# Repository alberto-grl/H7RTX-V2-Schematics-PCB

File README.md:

Schematics and PCB for a three-band direct sampling SDR. Using the internal ADC of an MCU, TX power is about 5 W.    
USB powered.    
Firmware code: https://github.com/alberto-grl/750RTX

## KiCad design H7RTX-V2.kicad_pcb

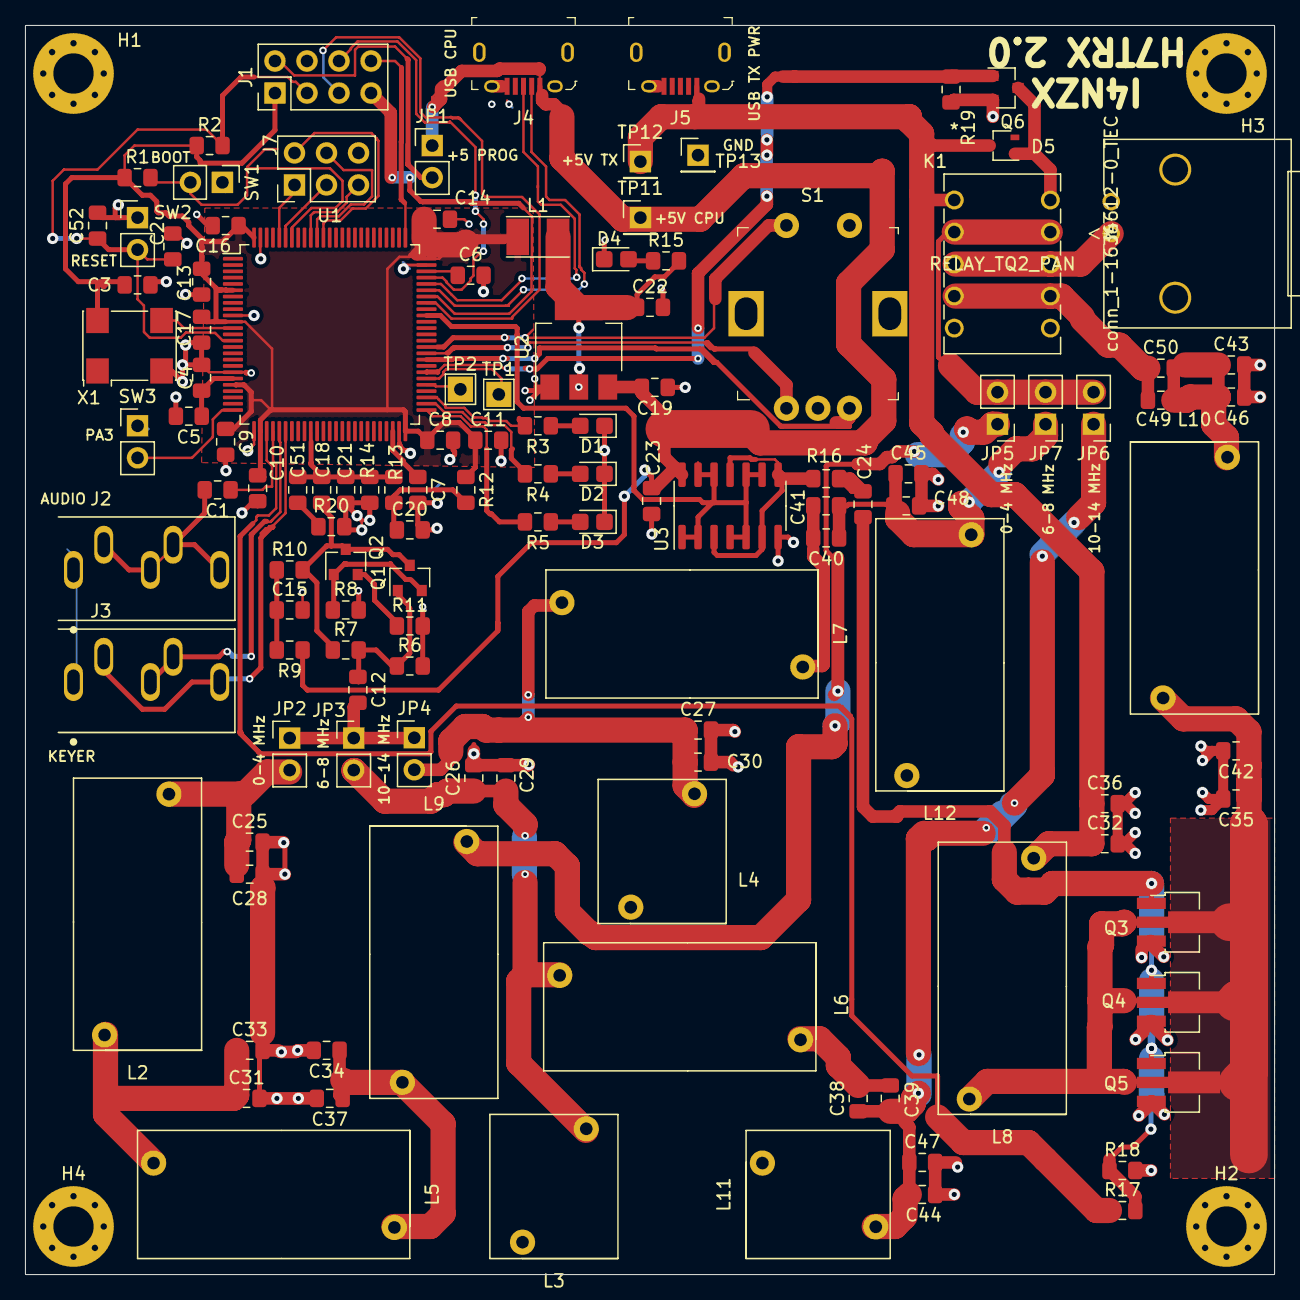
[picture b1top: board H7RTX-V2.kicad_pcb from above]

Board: 2 copper layers, 99.1 x 99.1 mm, 127 parts (0 on the bottom side), 71 nets.

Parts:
C1, C19, C22: 10u; C_0805_2012Metric_Pad1.15x1.40mm_HandSolder
C2, C3, C5, C6, C7, C8, C9, C10, C11, C13, C14, C17, C18, C23, C24, C32, C36, C49, C50: 100n; C_0805_2012Metric_Pad1.15x1.40mm_HandSolder
C4: 1u; C_0805_2012Metric_Pad1.15x1.40mm_HandSolder
C12, C51, C52: 10n; C_0805_2012Metric_Pad1.15x1.40mm_HandSolder
C15, C20: 470n; C_0805_2012Metric_Pad1.15x1.40mm_HandSolder
C16: 4.7u; C_0805_2012Metric_Pad1.15x1.40mm_HandSolder
C21, C39: 10p; C_0805_2012Metric_Pad1.15x1.40mm_HandSolder
C25: 2n; C_0805_2012Metric_Pad1.15x1.40mm_HandSolder
C26, C47: 2700p; C_0805_2012Metric_Pad1.15x1.40mm_HandSolder
C27, C30, C40, C41, C45, C48: C; C_0805_2012Metric_Pad1.15x1.40mm_HandSolder
C28, C31, C34: 0; C_0805_2012Metric_Pad1.15x1.40mm_HandSolder
C29, C44: 470p; C_0805_2012Metric_Pad1.15x1.40mm_HandSolder
C33: 1800p; C_0805_2012Metric_Pad1.15x1.40mm_HandSolder
C35, C42: 6800p; C_0805_2012Metric_Pad1.15x1.40mm_HandSolder
C37: 1000p; C_0805_2012Metric_Pad1.15x1.40mm_HandSolder
C38: 22p; C_0805_2012Metric_Pad1.15x1.40mm_HandSolder
C43: 470; C_0805_2012Metric_Pad1.15x1.40mm_HandSolder
C46: 2200p; C_0805_2012Metric_Pad1.15x1.40mm_HandSolder
D1, D4: RED; LED_0805_2012Metric_Castellated
D2: GREEN; LED_0805_2012Metric_Castellated
D3: YLW; LED_0805_2012Metric_Castellated
D5: BAS16W; SOT-323_SC-70
H1, H2, H3, H4: MountingHole_Pad; MountingHole_3.2mm_M3_Pad_Via
J1: Conn_02x04_Odd_Even; PinHeader_2x04_P2.54mm_Vertical
J2, J3: SJ1-3535NG; CUI_SJ1-3535NG
J4, J5: 10118194-0001LF; USB_Micro_B_Female_10118194-0001LF
J6: conn_1-1634612-0_TEC; 1-1634612-0
J7: Conn_02x03_Odd_Even; PinHeader_2x03_P2.54mm_Vertical
JP1, JP2, JP3, JP4, JP5, JP6, JP7: Jumper; PinHeader_1x02_P2.54mm_Vertical
K1: RELAY_TQ2_PAN; TQ2-5V
L1: NRH3012T100MN; L_Taiyo-Yuden_NR-30xx_HandSoldering
L2: 2.6u; Air_Wound_Coil_8x20
L3, L4: L; Air_Wound_Coil_8x10
L5: 4.3u; Air_Wound_Coil_8x20
L6: 16u; Air_Wound_Coil_8x20
L7, L12: L; Air_Wound_Coil_8x20
L8: 15u; Air_Wound_Coil_8x20
L9: 5.19u; Air_Wound_Coil_8x20
L10: 0.15u 8t 8mm x 15mm; Air_Wound_Coil_8x20
L11: 150n 5T 8 x 5; Air_Wound_Coil_8x10
Q1, Q2: PMBT2222A_215; SOT-23
Q3, Q4, Q5: ZXMN3A01ZTA; SOT-89-3_Handsoldering
Q6: BSS138; SOT-23
R1, R2: 10K; R_0805_2012Metric_Pad1.15x1.40mm_HandSolder
R3, R4, R5, R15: 220R; R_0805_2012Metric_Pad1.15x1.40mm_HandSolder
R6: 1200; R_0805_2012Metric_Pad1.15x1.40mm_HandSolder
R7: 1000; R_0805_2012Metric_Pad1.15x1.40mm_HandSolder
R8: 220; R_0805_2012Metric_Pad1.15x1.40mm_HandSolder
R9: 10; R_0805_2012Metric_Pad1.15x1.40mm_HandSolder
R10: 150; R_0805_2012Metric_Pad1.15x1.40mm_HandSolder
R11: 1.2; R_0805_2012Metric_Pad1.15x1.40mm_HandSolder
R12, R20: 100; R_0805_2012Metric_Pad1.15x1.40mm_HandSolder
R13, R14: 10k; R_0805_2012Metric_Pad1.15x1.40mm_HandSolder
R16: 2.2; R_0805_2012Metric_Pad1.15x1.40mm_HandSolder
R17: 1K; R_0805_2012Metric_Pad1.15x1.40mm_HandSolder
R18: 100K; R_0805_2012Metric_Pad1.15x1.40mm_HandSolder
R19: R; R_0805_2012Metric_Pad1.15x1.40mm_HandSolder
S1: PEC11R-4215F-S0024; Rotary_Encoder_Switched_PEC11R
SW1, SW2, SW3: SW_DIP_x01; PinHeader_1x02_P2.54mm_Vertical
TP1, TP2: TestPoint; TestPoint_THTPad_2.0x2.0mm_Drill1.0mm
TP11, TP12, TP13: TestPoint; PinHeader_1x01_P2.54mm_Vertical
U1: STM32H750VBT6; LQFP-100_14x14mm_P0.5mm
U2: AP1117-33; SOT-223-3_TabPin2
U3: 74ACT00DR; SOIC-14_3.9x8.7mm_P1.27mm
X1: ASV-25MHz; Oscillator_SMD_Abracon_ASV-4Pin_7.0x5.1mm

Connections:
+5V: C19.2, C23.1, J4.1, JP1.1, R9.1, TP11.1, U2.3, U3.14
+5VP: C32.1, C36.1, D5.3, J5.1, K1.1, L8.1, TP12.1
/BOOT: R1.2, SW1.2, U1.94
/I2C_SCL: J7.3, U1.95
/I2C_SDA: J7.1, U1.96
/KeyerDash: J3.3, J3.5, U1.30
/KeyerDot: J3.2, J3.4, U1.31
/PA3: SW3.2, U1.25
/PA4: C1.1, U1.28
/PB1: C18.1, C21.1, C51.1, R13.2, R14.1, U1.35
/PB3: J7.2, U1.89
/PB4: J7.4, U1.90
/PB5: J7.5, U1.91
/PB12: R5.2, U1.51
/PB13: R4.2, U1.52
/PB14: R3.2, U1.53
/PD8: TP2.1, U1.55
/PD9: TP1.1, U1.56
/PD12: S1.B, U1.59
/PD13: S1.A, U1.60
/PD14: S1.1, U1.61
/SWCLK: J1.8, U1.76
/SWDIO: J1.6, U1.72
/USB1_D+: J4.3, U1.71
/USB1_D-: J4.2, U1.70
/VCC_CPU: C3.1, C8.1, C9.1, C10.1, C11.1, C13.1, C14.1, C16.1, C17.1, J1.1, L1.1, R1.1, R2.1, R12.1, U1.6, U1.11, U1.21, U1.27, U1.50, U1.75, U1.100, X1.4
/VCP_RX: J1.7, U1.69
/VCP_TX: J1.5, U1.68
/nRESET: C2.1, C52.1, J1.3, R2.2, SW2.2, U1.14
GND: C2.2, C3.2, C4.2, C5.2, C6.2, C7.2, C8.2, C9.2, C10.2, C11.2, C13.2, C14.2, C15.2, C16.2, C17.2, C19.1, C20.2, C21.2, C22.2, C23.2, C25.2, C26.2, C27.2, C28.2, C29.2, C30.2, C31.2, C32.2, C33.2, C34.2, C35.2, C36.2, C37.2, C42.2, C43.2, C44.2, C45.2, C46.2, C47.2, C48.2, C52.2, D1.1, D2.1, D3.1, D4.1, H1.1, H2.1, H3.1, H4.1, J1.4, J2.1, J3.1, J4.5, J4.SH, J5.5, J5.SH, J6.2, J6.3, J6.4, J7.6, L3.2, L4.2, L11.2, L12.2, Q3.3, Q4.3, Q5.3, Q6.2, R6.2, R8.2, R11.2, R14.2, R18.2, R19.2, R20.2, S1.2, S1.3, S1.C, SW1.1, SW2.1, SW3.1, TP13.1, U1.10, U1.19, U1.26, U1.49, U1.74, U1.99, U2.1, U3.7, X1.2
MCO: U1.66, U3.1, U3.2, U3.4, U3.5, U3.9, U3.10, U3.12, U3.13
unnamed: C1.2, J2.2, J2.3, J2.4, J2.5
unnamed: C4.1, C5.1, U1.20
unnamed: C6.1, U1.73
unnamed: C7.1, U1.48
unnamed: C12.1, Q1.1, R6.1, R7.2
unnamed: C15.1, R9.2, R10.1
unnamed: C18.2, Q1.3, Q2.3, R7.1, R10.2
unnamed: C20.1, R12.2, R13.1
unnamed: C24.1, Q3.1, Q4.1, Q5.1, R17.2, R18.1
unnamed: C24.2, R16.1
unnamed: C25.1, C28.1, JP2.2, L2.1
unnamed: C26.1, C29.1, JP3.2, L3.1, L6.1
unnamed: C27.1, C30.1, JP4.2, L4.1, L7.1
unnamed: C31.1, C33.1, L2.2, L5.1
unnamed: C34.1, C37.1, L5.2, L9.1
unnamed: C35.1, C42.1, L8.2, L10.1, Q3.2, Q4.2, Q5.2
unnamed: C38.1, C39.1, C44.1, C47.1, JP6.1, L11.1
unnamed: C38.2, C39.2, L6.2
unnamed: C40.1, C41.1, C45.1, C48.1, JP7.1, L12.1
unnamed: C40.2, C41.2, L7.2
unnamed: C43.1, C46.1, C49.2, C50.2, L10.2
unnamed: C49.1, C50.1, K1.4, K1.7
unnamed: C51.2, R20.1
unnamed: D1.2, R3.1
unnamed: D2.2, R4.1
unnamed: D3.2, R5.1
unnamed: D4.2, R15.1
unnamed: D5.1, K1.10, Q6.3
unnamed: J1.2, JP1.2
unnamed: J6.1, K1.3, K1.8
unnamed: JP5.1, L9.2
unnamed: JP5.2, JP6.2, JP7.2, K1.2, K1.9
unnamed: Q1.2, Q2.1, R8.1
unnamed: Q2.2, R11.1
unnamed: R16.2, U3.3, U3.6, U3.8, U3.11
unnamed: U1.12, X1.3
RXTX: Q6.1, R19.1, U1.57
RX_IN: C12.2, JP2.1, JP3.1, JP4.1
TX_BIAS: R17.1, U1.29
VCC: C22.1, L1.2, R15.2, U2.2

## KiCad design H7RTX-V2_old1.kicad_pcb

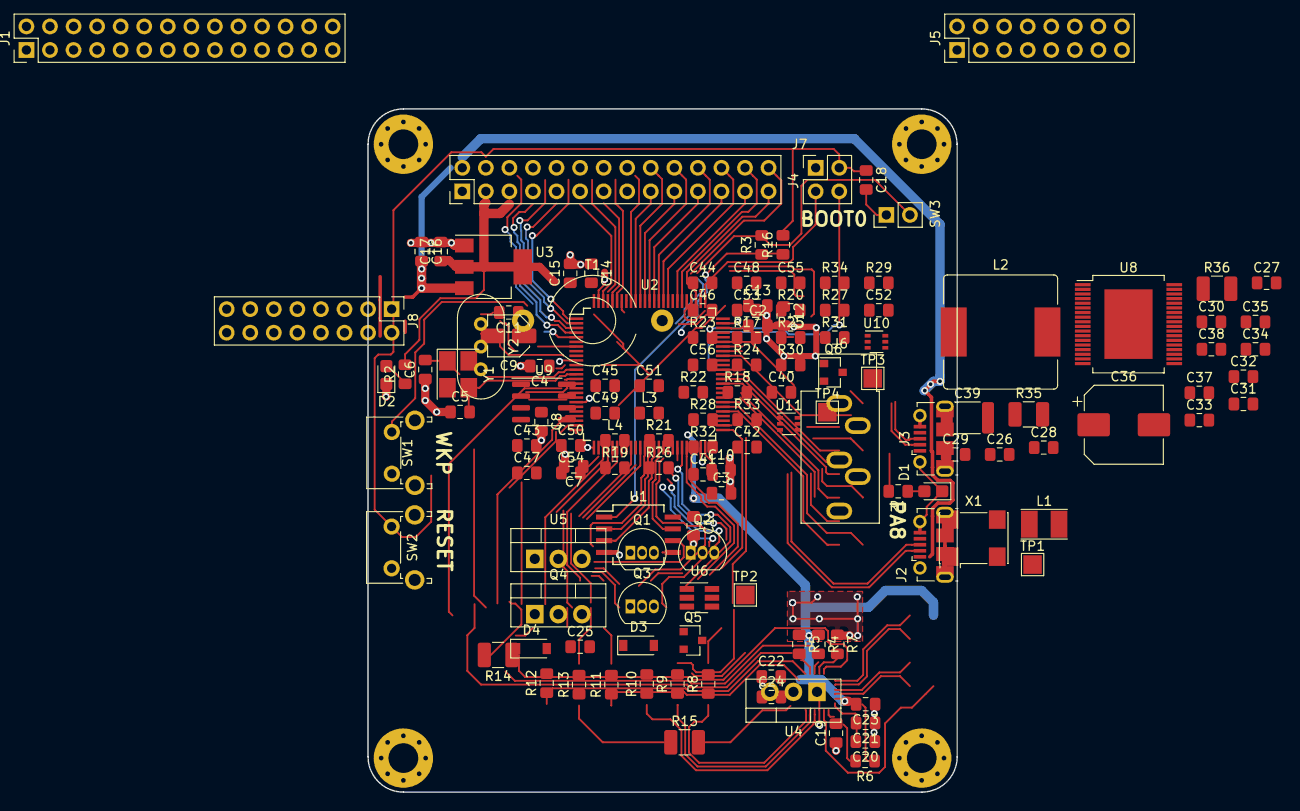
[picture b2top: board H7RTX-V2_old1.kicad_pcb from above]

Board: 2 copper layers, 63.5 x 73.7 mm, 139 parts (0 on the bottom side), 133 nets.

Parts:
C1, C2, C3, C4, C7, C8, C10, C12, C13, C14, C18, C23, C24, C26, C28, C29, C31, C32, C37, C38, C44, C45, C46, C47, C50, C54, C56: 100n; C_0805_2012Metric_Pad1.15x1.40mm_HandSolder
C5, C6: 18p; C_0805_2012Metric_Pad1.15x1.40mm_HandSolder
C9: 10u; C_Elec_4x5.4
C11, C22, C30, C34: 1u; C_0805_2012Metric_Pad1.15x1.40mm_HandSolder
C15: 4.7u; C_0805_2012Metric_Pad1.15x1.40mm_HandSolder
C16, C17, C19, C20, C21: 10u; C_0805_2012Metric_Pad1.15x1.40mm_HandSolder
C25, C40, C42, C48, C51, C53, C55: 10n; C_0805_2012Metric_Pad1.15x1.40mm_HandSolder
C27, C33: 220n; C_0805_2012Metric_Pad1.15x1.40mm_HandSolder
C35: 330p; C_0805_2012Metric_Pad1.15x1.40mm_HandSolder
C36: 220u; CP_Elec_8x10
C39: 220n polyester; C_1812_4532Metric_Pad1.30x3.40mm_HandSolder
C41: C; C_0805_2012Metric_Pad1.15x1.40mm_HandSolder
C43: 10p; C_0805_2012Metric_Pad1.15x1.40mm_HandSolder
C49, C52: 0; C_0805_2012Metric_Pad1.15x1.40mm_HandSolder
D1, D2: RED; LED_0805_2012Metric_Castellated
D3: D; D_SOD-123
D4: MMBD914LT3G; D_SOD-123
H1, H2, H3, H4: MountingHole_Pad; MountingHole_3.2mm_M3_Pad_Via
J1, J4: Conn_02x14_Odd_Even; PinHeader_2x14_P2.54mm_Vertical
J2, J3: USB_B_Micro; USB_Micro-B_Molex-105017-0001
J5, J8: Conn_02x08_Odd_Even; PinHeader_2x08_P2.54mm_Vertical
J6: AudioJack3; Jack_3.5mm_CUI_SJ1-3535NG_Horizontal
J7: Conn_02x02_Odd_Even; PinHeader_2x02_P2.54mm_Vertical
L1: NRH3012T100MN; L_Taiyo-Yuden_NR-30xx_HandSoldering
L2: 47u SRR1210-470M; L_Bourns_SRR1210A
L3, L4: 10u; L_0805_2012Metric_Pad1.15x1.40mm_HandSolder
Q1, Q2, Q3: BS170; TO-92_Inline
Q4: IRF540N; TO-220-3_Vertical
Q5: BSS138; SOT-23
Q6: MMBT2222; SOT-23
R1, R2: 220R; R_0805_2012Metric_Pad1.15x1.40mm_HandSolder
R3, R13, R16: 10K; R_0805_2012Metric_Pad1.15x1.40mm_HandSolder
R4, R5, R17, R25, R33, R34: 0; R_0805_2012Metric_Pad1.15x1.40mm_HandSolder
R6, R7, R10, R12, R18, R21, R22: 10k; R_0805_2012Metric_Pad1.15x1.40mm_HandSolder
R8: 2.2; R_0805_2012Metric_Pad1.15x1.40mm_HandSolder
R9: 1K; R_0805_2012Metric_Pad1.15x1.40mm_HandSolder
R11: 330; R_0805_2012Metric_Pad1.15x1.40mm_HandSolder
R14: 20 0.25W; R_1210_3225Metric_Pad1.42x2.65mm_HandSolder
R15: 6.2 0.25 W; R_1210_3225Metric_Pad1.42x2.65mm_HandSolder
R19: 3k3; R_0805_2012Metric_Pad1.15x1.40mm_HandSolder
R20, R23, R26, R28, R31: 100; R_0805_2012Metric_Pad1.15x1.40mm_HandSolder
R24, R27: 100k; R_0805_2012Metric_Pad1.15x1.40mm_HandSolder
R29: 62k; R_0805_2012Metric_Pad1.15x1.40mm_HandSolder
R30: 150k; R_0805_2012Metric_Pad1.15x1.40mm_HandSolder
R32: 2k2; R_0805_2012Metric_Pad1.15x1.40mm_HandSolder
R35, R36: 0; R_1210_3225Metric_Pad1.42x2.65mm_HandSolder
SW1, SW2: SW_Push; SW_Tactile_SPST_Angled_PTS645Vx31-2LFS
SW3: SW_DIP_x01; PinHeader_1x02_P2.54mm_Vertical
T1: Transformer_1P_1S_SO8; L_Toroid_Horizontal_D9.5mm_P15.00mm_Diameter10-5mm_Amidon-T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
TP1, TP2, TP3, TP4: TestPoint; TestPoint_Pad_2.0x2.0mm
U1: S25FL132K0XMFI010; SO-8_5.3x6.2mm_P1.27mm
U2: STM32H750VBT6; LQFP-100_14x14mm_P0.5mm
U3: AP1117-33; SOT-223-3_TabPin2
U4: LM7805_TO220; TO-220-3_Vertical
U5: LM7812_TO220; TO-220-3_Vertical
U6: LM5134AMF_NOPB; SOT-23-6_Handsoldering
U8: STA510; ST_PowerSSO-36_SlugDown
U9: SA612; SOIC-8_3.9x4.9mm_P1.27mm
U10, U11: BGA2869; SOT-363_SC-70-6
X1: ASV-xxxMHz; Oscillator_SMD_Abracon_ASV-4Pin_7.0x5.1mm
Y1: 16MHz; Crystal_SMD_3225-4Pin_3.2x2.5mm_HandSoldering
Y2: ECS-10.7-7.5B; Crystal_HC49-U-3Pin_Vertical

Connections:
+5V: C16.2, J4.2, R4.2, R5.1, R20.1, R26.1, R28.1, R31.1, U3.3
+24V: C19.1, C21.1, C27.1, C30.1, C33.1, C34.1, C36.1, D4.1, J8.1, J8.3, U4.1, U5.1, U8.4, U8.7, U8.12, U8.15
/BOOT: R3.2, SW3.2, U2.94
/IO0: U1.5, U2.37
/IO1: U1.2, U2.38
/IO2: U1.3, U2.39
/IO3: U1.7, U2.40
/PA0: J1.5, U2.22
/PA1: J1.6, U2.23
/PA2: J1.7, U2.24
/PA3: J1.8, U2.25
/PA4: C9.1, J1.9, U2.28
/PA5: J1.10, U2.29
/PA6: J1.11, U2.30
/PA7: J1.12, U2.31
/PA8: J5.4, R1.2, U2.67
/PA9: J5.1, U2.68
/PA10: J5.2, U2.69
/PA15: J4.28, U2.77
/PB0: J1.15, TP1.1, U2.34
/PB3: J4.19, U2.89
/PB4: J4.18, U2.90
/PB5: J4.17, U2.91
/PB6: J4.16, U2.92
/PB7: J4.15, U2.93
/PB8: J4.14, U2.95
/PB9: J4.13, U2.96
/PB10: J1.22, U2.46
/PB11: J1.23, U2.47
/PB12: J1.24, U2.51
/PB13: J1.25, U2.52
/PC0: J1.1, U2.15
/PC1: J1.2, U2.16
/PC2: J1.3, U2.17
/PC4: J1.13, U2.32
/PC5: J1.14, U2.33
/PC7: J5.6, U2.64
/PC10: J4.27, U2.78
/PC13: SW1.2, U2.7
/PD0: J4.26, U2.81
/PD1: J4.25, U2.82
/PD3: J4.24, U2.84
/PD4: J4.23, U2.85
/PD5: J4.22, U2.86
/PD6: J4.21, U2.87
/PD7: J4.20, U2.88
/PD8: J5.13, U2.55
/PD9: J5.14, U2.56
/PD10: J5.11, U2.57
/PD11: J5.12, U2.58
/PD12: J5.9, U2.59
/PD13: J5.10, U2.60
/PD14: J5.7, U2.61
/PD15: J5.8, U2.62
/PE1: J4.11, U2.98
/PE3: J4.9, U2.2
/PE4: J4.8, U2.3
/PE5: J4.7, U2.4
/PE6: J4.6, U2.5
/PE14: J1.20, U2.44
/PE15: J1.21, U2.45
/SCLK: U1.6, U2.36
/SWCLK: J7.3, U2.76
/SWDIO: J7.4, U2.72
/USB0_D+: J2.3, U2.54
/USB0_D-: J2.2, U2.53
/USB1_D+: J3.3, U2.71
/USB1_D-: J3.2, U2.70
/VCC_CPU: C1.1, C4.1, C7.1, C8.1, C10.1, C12.1, C13.1, C15.1, L1.1, U1.8, U2.6, U2.11, U2.21, U2.27, U2.50, U2.75, U2.100, X1.4
/nCS: U1.1, U2.79
/nRESET: C18.1, J4.4, J7.2, R16.2, SW2.2, U2.14
A_FAULT: C32.1, J1.19, U2.43, U8.27, U8.28
A_PWM: J1.17, J5.5, U2.41, U2.63, U8.31, U8.32
A_PWRDN: J1.18, U2.42, U8.25
GND: C1.2, C2.2, C3.2, C4.2, C5.1, C6.1, C7.2, C8.2, C10.2, C11.2, C12.2, C13.2, C14.2, C15.2, C16.1, C17.2, C18.2, C19.2, C20.2, C21.2, C22.2, C23.2, C24.2, C25.2, C26.2, C27.2, C28.2, C30.2, C32.2, C33.2, C34.2, C35.2, C36.2, C37.2, C39.2, C41.2, C43.2, C44.2, C46.2, C49.2, C50.2, C52.2, C54.2, C56.2, D1.1, D2.1, H1.1, H2.1, H3.1, H4.1, J1.26, J1.27, J1.28, J2.5, J2.6, J3.5, J3.6, J4.1, J5.15, J5.16, J6.T, J7.1, J8.13, J8.15, Q1.3, Q2.3, Q3.3, Q4.3, Q5.2, R7.2, R9.2, R11.2, R12.2, R13.2, R19.2, R22.2, R24.2, R27.2, R30.2, R32.2, SW1.1, SW2.1, SW3.1, U1.4, U2.10, U2.19, U2.26, U2.49, U2.74, U2.99, U3.1, U4.2, U5.2, U6.4, U8.1, U8.5, U8.6, U8.13, U8.14, U8.19, U8.29, U8.30, U9.3, U10.2, U10.4, U10.5, U11.2, U11.4, U11.5, X1.2, Y2.2
MCO: J5.3, R7.1, R18.1, U2.66, U6.6
MODUL_OUT: C38.1, C39.1, J8.5, J8.7, L2.2, R15.1
unnamed: C2.1, U2.73
unnamed: C3.1, U2.48
unnamed: C5.2, U2.13, Y1.3
unnamed: C6.2, U2.12, X1.3, Y1.1
unnamed: C9.2, J6.R, J6.S
unnamed: C11.1, C14.1, U2.20
unnamed: C20.1, R5.2, U4.3
unnamed: C22.1, C23.1, C24.1, U5.3, U6.1
unnamed: C28.1, C31.1, U8.35, U8.36
unnamed: C29.1, U8.21, U8.22
unnamed: C29.2, U8.20
unnamed: C31.2, U8.33, U8.34
unnamed: C35.1, R14.2
unnamed: C37.1, C38.2, R15.2
unnamed: C40.1, T1.1
unnamed: C40.2, R17.1
unnamed: C41.1, U9.2
unnamed: C42.1, U9.6
unnamed: C42.2, R18.2, R19.1
unnamed: C44.1, R21.1, R23.2
unnamed: C45.1, C47.2, R24.1
unnamed: C46.1, R20.2, U9.8
unnamed: C47.1, L3.2, U10.3
unnamed: C48.1, C49.1, Y2.1
unnamed: C48.2, R25.1
unnamed: C50.1, L3.1, R26.2, U10.1
unnamed: C51.1, L4.2, U11.3
unnamed: C51.2, U10.6
unnamed: C52.1, C53.2, R27.1, TP4.1, Y2.3
unnamed: C53.1, Q6.1, R29.2, R30.1
unnamed: C54.1, L4.1, R28.2, U11.1
unnamed: C55.1, R33.2, R34.1
unnamed: C55.2, U11.6
unnamed: C56.1, Q6.3, R29.1, R31.2
unnamed: D1.2, R1.1
unnamed: D2.2, R2.1
unnamed: D3.2, R10.2, R11.1
unnamed: D4.2, J8.12, Q5.3
unnamed: J2.1, J3.1, R4.1
unnamed: J8.9, J8.11, Q1.1, Q2.1, Q3.1, Q4.2, R10.1, TP2.1
unnamed: L2.1, R14.1, R35.1, R36.1
unnamed: Q1.2, Q2.2, Q3.2, Q4.1, R8.1, R9.1
unnamed: Q6.2, R32.1, R34.2
unnamed: R8.2, U6.3
unnamed: R25.2, U9.4
unnamed: R35.2, U8.10, U8.11
unnamed: R36.2, U8.16, U8.17
unnamed: U8.2, U8.3
unnamed: U8.8, U8.9
RF_ADC_IN: C43.1, C45.2, J1.16, R21.2, R22.1, TP3.1, U2.35
RF_IN_1: J8.14, R17.2
RF_IN_2: J8.16, R33.1
RXTX: J4.12, Q5.1, R13.1, U2.97
TXV: C25.1, D3.1, J1.4, R12.1, U2.18
TX_ENA: J4.10, R6.2, U2.1, U6.5
VCC: C17.1, C26.1, J4.3, J4.5, L1.2, R2.2, R3.1, R6.1, R16.1, R23.1, U3.2, U8.23, U8.24, U8.26

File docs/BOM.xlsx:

Reference | Quantity | Value | Footprint | Datasheet | Manufacturer | PartNumber | MANUFACTURER | PARTREV | SNAPEDA_PACKAGE_ID | STANDARD
C11 C22 C30 C34 | 4 | 1u | Capacitor_SMD:C_0805_2012Metric_Pad1.15x1.40mm_HandSolder | ~
C15 | 1 | 4.7u | Capacitor_SMD:C_0805_2012Metric_Pad1.15x1.40mm_HandSolder | ~ | Wurth Electronics Inc | 885012107013
C16 C17 C19 C20 C21 | 5 | 10u | Capacitor_SMD:C_0805_2012Metric_Pad1.15x1.40mm_HandSolder | ~ | Samsung Electro-Mechanics | CL21A106KOQNNWE
C25 C40 C42 C48 C51 C53 C55 | 7 | 10n | Capacitor_SMD:C_0805_2012Metric_Pad1.15x1.40mm_HandSolder | ~
C27 C33 | 2 | 220n | Capacitor_SMD:C_0805_2012Metric_Pad1.15x1.40mm_HandSolder | ~
C35 | 1 | 330p | Capacitor_SMD:C_0805_2012Metric_Pad1.15x1.40mm_HandSolder | ~
C36 | 1 | 220u | Capacitor_SMD:CP_Elec_8x10 | ~
C39 | 1 | 220n polyester | Capacitor_SMD:C_1812_4532Metric_Pad1.30x3.40mm_HandSolder | ~
C1 C2 C3 C4 C7 C8 C10 C12 C13 C14 C18 C23 C24 C26 C28 C29 C31 C32 C37 C38 C44 C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 | 28 | 100n | Capacitor_SMD:C_0805_2012Metric_Pad1.15x1.40mm_HandSolder | ~ | Wurth Electronics Inc | 885012207045
C43 | 1 | 10p | Capacitor_SMD:C_0805_2012Metric_Pad1.15x1.40mm_HandSolder | ~
C49 C52 | 2 | 0 | Capacitor_SMD:C_0805_2012Metric_Pad1.15x1.40mm_HandSolder | ~
C5 C6 | 2 | 18p | Capacitor_SMD:C_0805_2012Metric_Pad1.15x1.40mm_HandSolder | ~ | Samsung Electro-Mechanics | CL21C180JBANNNC
C58 | 1 | 1n | Capacitor_SMD:C_0805_2012Metric_Pad1.15x1.40mm_HandSolder | ~
C41 C59 | 2 | C | Capacitor_SMD:C_0805_2012Metric_Pad1.15x1.40mm_HandSolder | ~
C9 C57 | 2 | 10u | Capacitor_SMD:C_Elec_4x5.4 | ~
D1 D2 | 2 | RED | LED_SMD:LED_0805_2012Metric_Castellated | ~ | Wurth Electronics Inc | 150080GS75000
D3 | 1 | D | Diode_SMD:D_SOD-123 | ~
D4 | 1 | MMBD914LT3G | Diode_SMD:D_SOD-123 | ~
H1 H2 H3 H4 H5 | 5 | MountingHole_Pad | MountingHole:MountingHole_3.2mm_M3_Pad_Via | ~ | - | -
J12 J13 | 2 | Conn_01x02 | Connector_PinHeader_2.54mm:PinHeader_1x02_P2.54mm_Vertical | ~
J2 | 1 | USB_B_Micro | Connector_USB:USB_Micro-B_Amphenol_10104110_Horizontal | ~
J4 | 1 | Conn_02x14_Odd_Even | Connector_PinHeader_2.54mm:PinHeader_2x14_P2.54mm_Vertical | ~ | - | -
J1 J5 | 2 | Conn_02x08_Odd_Even | Connector_PinHeader_2.54mm:PinHeader_2x08_P2.54mm_Vertical | ~ | - | -
J6 J9 | 2 | AudioJack3 | Connector_Audio:Jack_3.5mm_CUI_SJ1-3535NG_Horizontal | ~
J3 J7 J10 J11 | 4 | Conn_02x02_Odd_Even | Connector_PinHeader_2.54mm:PinHeader_2x02_P2.54mm_Vertical | ~ | - | -
J8 | 1 | Screw_Terminal_01x02 | Connector_Phoenix_MSTB:PhoenixContact_MSTBA_2,5_2-G-5,08_1x02_P5.08mm_Horizontal | ~
L1 | 1 | NRH3012T100MN | Inductor_SMD:L_Taiyo-Yuden_NR-30xx_HandSoldering | ~
L2 | 1 | 47u SRR1210-470M | Inductor_SMD:L_Bourns_SRR1210A | ~
L3 L4 | 2 | 10u | Inductor_SMD:L_0805_2012Metric_Pad1.15x1.40mm_HandSolder | ~
Q1 Q2 Q3 | 3 | BS170 | Package_TO_SOT_THT:TO-92_Inline | http://www.fairchildsemi.com/ds/BS/BS170.pdf
Q4 | 1 | IRF540N | Package_TO_SOT_THT:TO-220-3_Vertical | http://www.irf.com/product-info/datasheets/data/irf540n.pdf
Q5 | 1 | BSS138 | Package_TO_SOT_SMD:SOT-23 | https://www.fairchildsemi.com/datasheets/BS/BSS138.pdf
Q6 | 1 | MMBT2222 | Package_TO_SOT_SMD:SOT-23 | https://www.fairchildsemi.com/datasheets/2N/2N3904.pdf
R11 | 1 | 330 | Resistor_SMD:R_0805_2012Metric_Pad1.15x1.40mm_HandSolder | ~
R14 | 1 | 20 0.25W | Resistor_SMD:R_1210_3225Metric_Pad1.42x2.65mm_HandSolder | ~
R15 | 1 | 6.2 0.25 W | Resistor_SMD:R_1210_3225Metric_Pad1.42x2.65mm_HandSolder | ~
R19 | 1 | 3k3 | Resistor_SMD:R_0805_2012Metric_Pad1.15x1.40mm_HandSolder | ~
R1 R2 | 2 | 220R | Resistor_SMD:R_0805_2012Metric_Pad1.15x1.40mm_HandSolder | ~ | TE Connectivity Passive Product | CRG0805F220R
R20 R23 R26 R28 R31 | 5 | 100 | Resistor_SMD:R_0805_2012Metric_Pad1.15x1.40mm_HandSolder | ~
R24 R27 | 2 | 100k | Resistor_SMD:R_0805_2012Metric_Pad1.15x1.40mm_HandSolder | ~
R29 | 1 | 62k | Resistor_SMD:R_0805_2012Metric_Pad1.15x1.40mm_HandSolder | ~
R3 R13 R16 | 3 | 10K | Resistor_SMD:R_0805_2012Metric_Pad1.15x1.40mm_HandSolder | ~ | TE Connectivity Passive Product | CRG0805F10K/10
R30 | 1 | 150k | Resistor_SMD:R_0805_2012Metric_Pad1.15x1.40mm_HandSolder | ~
R32 | 1 | 2k2 | Resistor_SMD:R_0805_2012Metric_Pad1.15x1.40mm_HandSolder | ~
R35 R36 | 2 | 0 | Resistor_SMD:R_1210_3225Metric_Pad1.42x2.65mm_HandSolder | ~
R37 R38 R39 | 3 | 10k | Resistor_SMD:R_1210_3225Metric_Pad1.42x2.65mm_HandSolder | ~
R4 R5 R17 R25 R33 R34 | 6 | 0 | Resistor_SMD:R_0805_2012Metric_Pad1.15x1.40mm_HandSolder | ~
R6 R7 R10 R12 R18 R21 R22 | 7 | 10k | Resistor_SMD:R_0805_2012Metric_Pad1.15x1.40mm_HandSolder | ~
R8 | 1 | 2.2 | Resistor_SMD:R_0805_2012Metric_Pad1.15x1.40mm_HandSolder | ~
R9 | 1 | 1K | Resistor_SMD:R_0805_2012Metric_Pad1.15x1.40mm_HandSolder | ~
SW1 SW2 SW3 | 3 | SW_DIP_x01 | Connector_PinHeader_2.54mm:PinHeader_1x02_P2.54mm_Vertical |  | - | -
T1 | 1 | Transformer_1P_1S | Transformer_THT:Transformer_Toroid_Horizontal_D14.0mm_Amidon-T50 | ~
TP1 TP2 TP3 TP4 TP5 | 5 | TestPoint | TestPoint:TestPoint_Pad_D1.0mm | ~
TP6 TP7 TP9 TP13 TP14 TP15 TP16 TP17 | 8 | TestPoint_Small | TestPoint:TestPoint_Pad_D1.0mm | ~
U1 | 1 | STA516BETR | footprints:SOP65P1420X343-36N |  |  |  | ST MICROELECTRONICS | 1 | 32471 | IPC-7351B
U10 U11 | 2 | BGA2869 | Package_TO_SOT_SMD:SOT-363_SC-70-6 | https://www.nxp.com/docs/en/data-sheet/BGA2869.pdf
U2 | 1 | STM32H750VBT6 | Package_QFP:LQFP-100_14x14mm_P0.5mm | DOCUMENTATION
U3 | 1 | AP1117-33 | Package_TO_SOT_SMD:SOT-223-3_TabPin2 | http://www.diodes.com/datasheets/AP1117.pdf | ON Semiconductor | NCP1117ST33T3G
U4 | 1 | LM7805_TO220 | Package_TO_SOT_THT:TO-220-3_Vertical | http://www.fairchildsemi.com/ds/LM/LM7805.pdf
U5 | 1 | LM7812_TO220 | Package_TO_SOT_THT:TO-220-3_Vertical | http://www.fairchildsemi.com/ds/LM/LM7805.pdf
U6 | 1 | LM5134AMF_NOPB | Package_TO_SOT_SMD:SOT-23-6_Handsoldering
U9 | 1 | SA612 | Package_SO:SOIC-8_3.9x4.9mm_P1.27mm
X1 | 1 | ASV-xxxMHz | Oscillator:Oscillator_SMD_Abracon_ASV-4Pin_7.0x5.1mm | http://www.abracon.com/Oscillators/ASV.pdf
Y1 | 1 | 16MHz | Crystal:Crystal_SMD_3225-4Pin_3.2x2.5mm_HandSoldering | ~ | EPSON | TSX-3225 16.0000MF09Z-AC0
Y2 | 1 | ECS-10.7-7.5B | Crystal:Crystal_HC49-U-3Pin_Vertical | ~

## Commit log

2026-02-28 Schematics and PCB used for first batch of 5 units
2026-02-28 Update README with SDR project details

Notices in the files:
parts and their libraries:
Copyright 2021 Accelerated Designs. All rights reserved.
